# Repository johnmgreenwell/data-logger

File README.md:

# Data Logger PCB Project

Custom PCB for Battery-Powered SD Card Data Logging

## Overview

This custom PCB incorporates an [Atmega328 microcontroller](https://www.digikey.com/en/products/detail/microchip-technology/ATMEGA328P-AU/1832260) interfaced with a [DS1037 RTC](https://www.digikey.com/en/products/detail/analog-devices-inc-maxim-integrated/DS1307Z/11523034) for time-keeping and a [MicroSD card slot](https://www.mouser.com/ProductDetail/Wurth-Elektronik/693072010801?qs=7gQLVZk5cPmw4uU1mAcUFg%3D%3D) for nonvolatile data write/read. The board may be powered with 3.3V externally or with a Li-Po battery able to be recharged on the board using adjacent 5V-GND pins and monitored by a [TP4054 linear charger IC](https://www.utsource.net/itm/p/5323872.html?digipart=1).

Pin header placement is designed to be breadboard-friendly. No components are soldered to the bottom of the board for space and simplicity consideration, as well as for opportunity to attach a coincell battery on the underside of the board for the RTC if desired. The board is designed in KiCad 5 with all source files available in the project [CAD directory](/cad).

## Usage

Interface with the SD card is accomplished by with the hardware SPI pins on the microcontroller, and similarly interface with the RTC is done with the hardware I2C pins. The SQW/OUT pin from the RTC is hard-wired to the INT0 pin on the microcontroller as input, allowing for events triggered on impulse from RTC signals, including wakeup from sleep modes for power-saving. Likewise, the VBAT pin on the RTC is available on an external pin so that a coincell battery may be attached to prevent time erasure on detachment of Li-Po or external battery.

Any suitable SPI SD library or I2C DS1307 RTC library may be used in the code for the microcontroller, provided the appropriate hardware protocols are utilized, as in the example code below.

```cpp
#include <TimeLib.h>
#include <DS1307RTC.h>
#include <SD.h>
...
tmElements_t tm;
File root;
...
const uint8_t INT0_PIN = 2;
const uint8_t CS_PIN = 10;
...
void setup(void) {
    bool parse=false;
    bool config=false;

    pinMode(INT0_PIN, INPUT);
    SPI.begin();
    Wire.begin();

    // Initialize RTC ref. DS1307RTC lib by Paul Stoffregen
    if (getDate(__DATE__) && getTime(__TIME__)) {
        parse = true;
        if (RTC.write(tm)) {
            config = true;
        }
  }

    // Initialize SD
    if (!SD.begin(CS_PIN)) {
        while (1);
    }
    root = SD.open("/");

}
...
```

## Schematic

The overall schematic for the test setup, along with its associated CAD files are included as composed in KiCad 5.

Improvements to this design could include silkscreen labels of pins for convenience, and possibly a re-orientation or expansion to the pin headers. Rather than VBAT as an external pin, footprint for a coincell battery holder might be added to the bottom of the board as optional. Additionally, the CHRG pin on the battery IC might be attached to an LED or tied back to the microcontroller for monitoring.

## License

MIT © 2022 John Greenwell

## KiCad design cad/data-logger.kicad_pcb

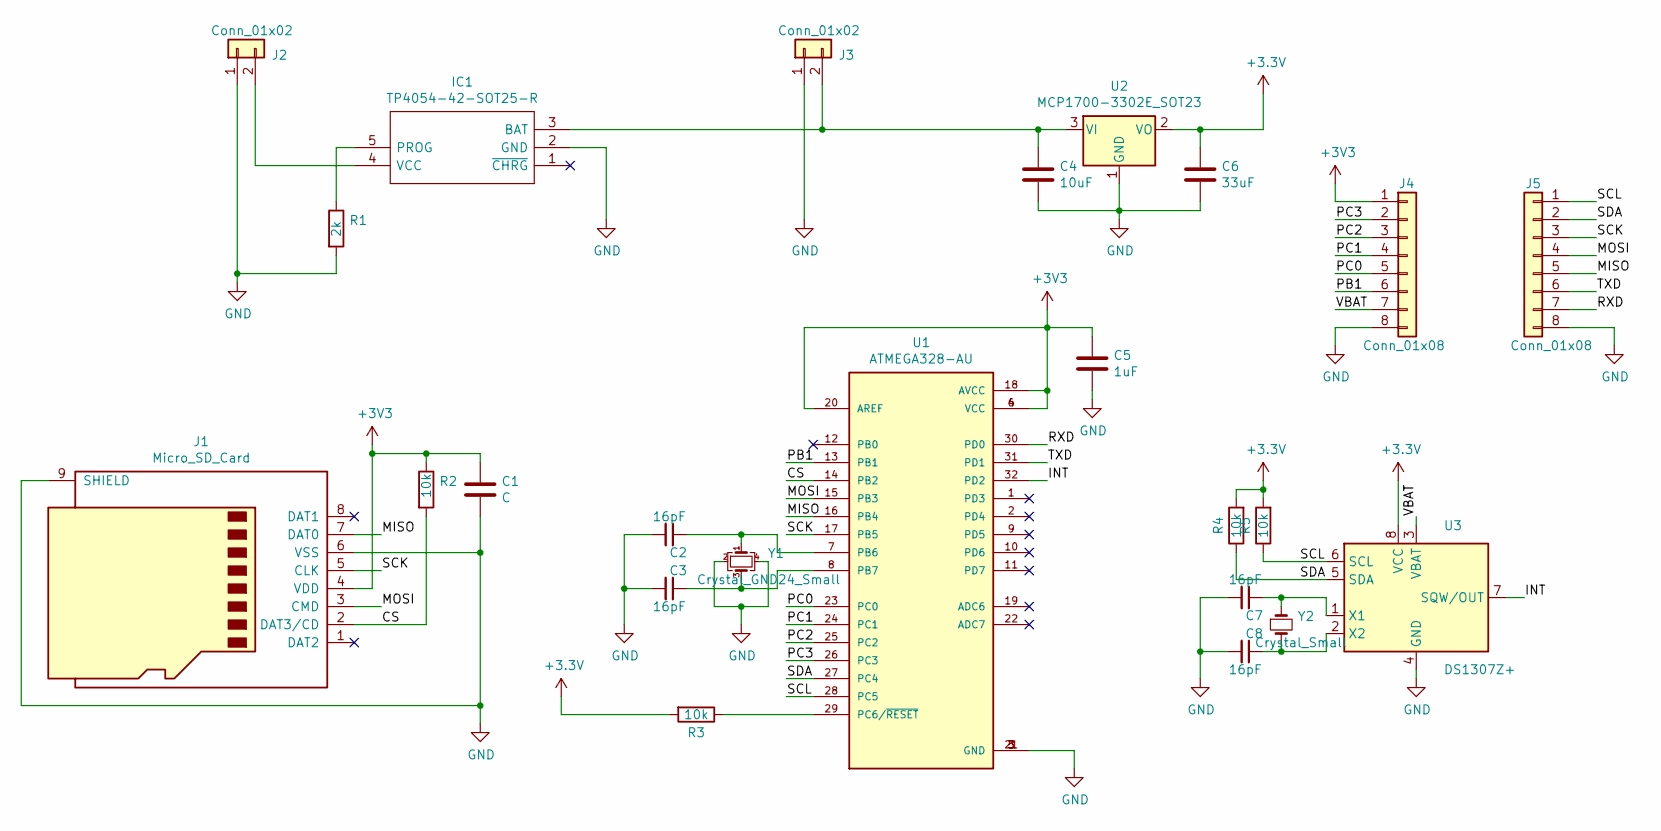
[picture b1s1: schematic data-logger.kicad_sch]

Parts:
C1: C; C_0603_1608Metric_Pad1.08x0.95mm_HandSolder
C2, C3, C7, C8: 16pF; C_0603_1608Metric_Pad1.08x0.95mm_HandSolder
C4: 10uF; C_0603_1608Metric_Pad1.08x0.95mm_HandSolder
C5: 1uF; C_0603_1608Metric_Pad1.08x0.95mm_HandSolder
C6: 33uF; C_0603_1608Metric_Pad1.08x0.95mm_HandSolder
IC1: TP4054-42-SOT25-R; SOT95P280X100-5N; Manufacturer_Part_Number TP4054-42-SOT25-R
J1: Micro_SD_Card; microSD_HC_Wuerth_693072010801
J2: Conn_01x02; PinHeader_1x02_P2.54mm_Vertical
J3: Conn_01x02; JST_PH_S2B-PH-K_1x02_P2.00mm_Horizontal
J4, J5: Conn_01x08; PinHeader_1x08_P2.54mm_Vertical
R1: 2k; R_0603_1608Metric_Pad0.98x0.95mm_HandSolder
R2, R3, R4, R5: 10k; R_0603_1608Metric_Pad0.98x0.95mm_HandSolder
U1: ATMEGA328-AU; QFP80P900X900X120-32N
U2: MCP1700-3302E_SOT23; SOT-23W_Handsoldering
U3: DS1307Z+; SOIC-8_3.9x4.9mm_P1.27mm
Y1: Crystal_GND24_Small; Crystal_SMD_TXC_7M-4Pin_3.2x2.5mm_HandSoldering
Y2: Crystal_Small; Crystal_C26-LF_D2.1mm_L6.5mm_Horizontal

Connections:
/CS: J1.2 (DAT3/CD), R2.2, U1.14 (PB2)
/INT: U1.32 (PD2), U3.7 (SQW/OUT)
/MISO: J1.7 (DAT0), J5.5, U1.16 (PB4)
/MOSI: J1.3 (CMD), J5.4, U1.15 (PB3)
/PB1: J4.6, U1.13 (PB1)
/PC0: J4.5, U1.23 (PC0)
/PC1: J4.4, U1.24 (PC1)
/PC2: J4.3, U1.25 (PC2)
/PC3: J4.2, U1.26 (PC3)
/RXD: J5.7, U1.30 (PD0)
/SCK: J1.5 (CLK), J5.3, U1.17 (PB5)
/SCL: J5.1, R5.1, U1.28 (PC5), U3.6 (SCL)
/SDA: J5.2, R4.1, U1.27 (PC4), U3.5 (SDA)
/TXD: J5.6, U1.31 (PD1)
/VBAT: J4.7, U3.3 (VBAT)
GND: C1.2, C2.2, C3.2, C4.2, C5.2, C6.2, C7.2, C8.2, IC1.2 (GND), J1.6 (VSS), J1.9 (SHIELD), J2.1, J3.1, J4.8, J5.8, R1.2, U1.3 (GND), U1.5 (GND), U1.21 (GND), U2.1 (GND), U3.4 (GND), Y1.2, Y1.4
unnamed: C2.1, U1.7 (PB6), Y1.1
unnamed: C3.1, U1.8 (PB7), Y1.3
unnamed: C4.1, IC1.3 (BAT), J3.2, U2.3 (VI)
unnamed: C7.1, U3.1 (X1), Y2.1
unnamed: C8.1, U3.2 (X2), Y2.2
unnamed: IC1.4 (VCC), J2.2
unnamed: IC1.5 (PROG), R1.1
unnamed: R3.1, U1.29 (PC6/~RESET)

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
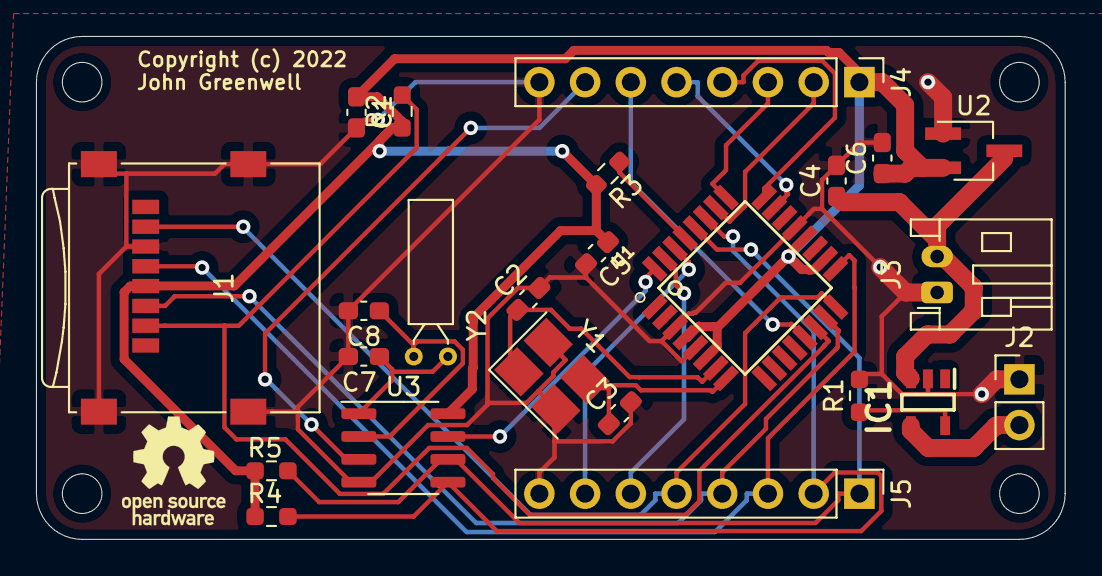
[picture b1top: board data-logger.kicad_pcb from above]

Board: 2 copper layers, 57.2 x 27.9 mm, 28 parts (0 on the bottom side), 25 nets.

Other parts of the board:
MH1, MH2, MH3, MH4: MountingHole_2.2mm_M2

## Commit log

2023-12-22 Update kicad schematic and layout files to support kicad 7
2025-05-02 Remove and ignore unnecessary auto-backup compressed files

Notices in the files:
cad/data-logger.kicad_pcb:
Copyright (c) 2022
